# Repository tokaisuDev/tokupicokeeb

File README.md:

# Welcome to this keyboard's repo!

This is a Raspberry Pi Pico W-powered keyboard based on Stenokeyboard's Polyglot and 1upkeyboards' pi40.

Well, this is in the *beta* testing version so hopefully I can hear you guys' opinions on this, because this is my first time designing a PCB for a keyboard. Mistakes can be made...

Thanks for reading! And looking at this markdown file, I guess.

P/s: More info will be added later, I'm lazy

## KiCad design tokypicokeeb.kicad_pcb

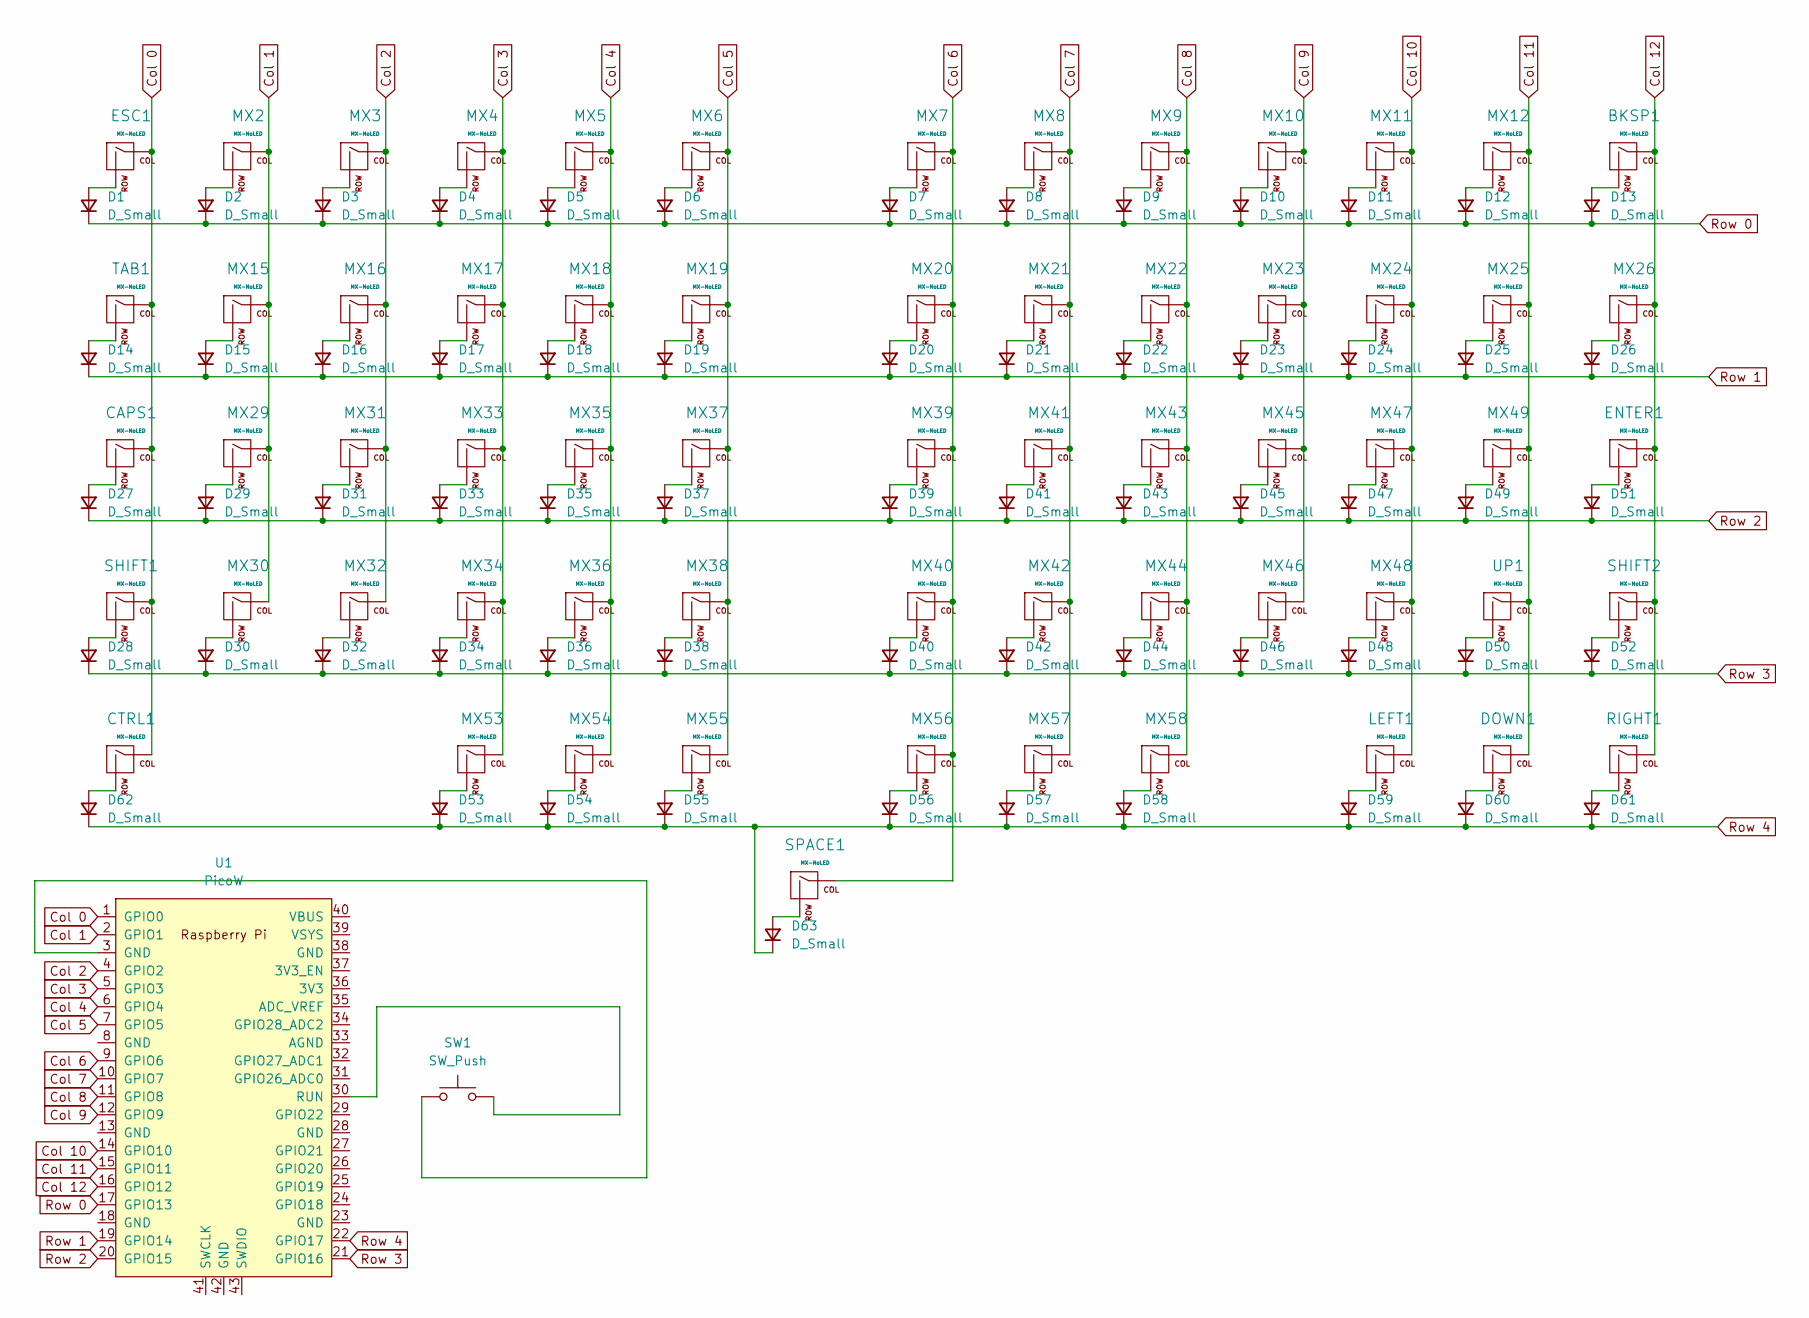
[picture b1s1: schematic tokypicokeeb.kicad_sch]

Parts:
BKSP1: MX-NoLED; MXOnly-2U-NoLED
CAPS1: MX-NoLED; MXOnly-1.75U-NoLED
CTRL1: MX-NoLED; MXOnly-1.25U-NoLED
D1, D2, D3, D4, D5, D6, D7, D8, D9, D10, D11, D12, D13, D14, D15, D16, D17, D18, D19, D20, D21, D22, D23, D24, D25, D26, D27, D28, D29, D30, D31, D32, D33, D34, D35, D36, D37, D38, D39, D40, D41, D42, D43, D44, D45, D46, D47, D48, D49, D50, D51, D52, D53, D54, D55, D56, D57, D58, D59, D60, D61, D62, D63: D_Small; Diode_DO-35
DOWN1: MX-NoLED; MXOnly-1U-NoLED
ENTER1: MX-NoLED; MXOnly-2.25U-NoLED
ESC1: MX-NoLED; MXOnly-1U-NoLED
LEFT1: MX-NoLED; MXOnly-1U-NoLED
MX2, MX3, MX4, MX5, MX6, MX7, MX8, MX9, MX10, MX11, MX12, MX15, MX16, MX17, MX18, MX19, MX20, MX21, MX22, MX23, MX24, MX25, MX29, MX30, MX31, MX32, MX33, MX34, MX35, MX36, MX37, MX38, MX39, MX40, MX41, MX42, MX43, MX44, MX45, MX46, MX47, MX48, MX49, MX53, MX54, MX55, MX56, MX57, MX58: MX-NoLED; MXOnly-1U-NoLED
MX26: MX-NoLED; MXOnly-1.5U-NoLED
RIGHT1: MX-NoLED; MXOnly-1U-NoLED
SHIFT1: MX-NoLED; MXOnly-2.25U-NoLED
SHIFT2: MX-NoLED; MXOnly-2.75U-NoLED
SPACE1: MX-NoLED; MXOnly-6.25U-NoLED
SW1: SW_Push; SKQG-1155865
TAB1: MX-NoLED; MXOnly-1.5U-NoLED
U1: PicoW; RPi_PicoW_SMD_TH
UP1: MX-NoLED; MXOnly-1U-NoLED

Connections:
Col 0: CAPS1.1 (COL), CTRL1.1 (COL), ESC1.1 (COL), SHIFT1.1 (COL), TAB1.1 (COL), U1.1 (GPIO0)
Col 1: MX2.1 (COL), MX15.1 (COL), MX29.1 (COL), MX30.1 (COL), U1.2 (GPIO1)
Col 2: MX3.1 (COL), MX16.1 (COL), MX31.1 (COL), MX32.1 (COL), U1.4 (GPIO2)
Col 3: MX4.1 (COL), MX17.1 (COL), MX33.1 (COL), MX34.1 (COL), MX53.1 (COL), U1.5 (GPIO3)
Col 4: MX5.1 (COL), MX18.1 (COL), MX35.1 (COL), MX36.1 (COL), MX54.1 (COL), U1.6 (GPIO4)
Col 5: MX6.1 (COL), MX19.1 (COL), MX37.1 (COL), MX38.1 (COL), MX55.1 (COL), U1.7 (GPIO5)
Col 6: MX7.1 (COL), MX20.1 (COL), MX39.1 (COL), MX40.1 (COL), MX56.1 (COL), SPACE1.1 (COL), U1.9 (GPIO6)
Col 7: MX8.1 (COL), MX21.1 (COL), MX41.1 (COL), MX42.1 (COL), MX57.1 (COL), U1.10 (GPIO7)
Col 8: MX9.1 (COL), MX22.1 (COL), MX43.1 (COL), MX44.1 (COL), MX58.1 (COL), U1.11 (GPIO8)
Col 9: MX10.1 (COL), MX23.1 (COL), MX45.1 (COL), MX46.1 (COL), U1.12 (GPIO9)
Col 10: LEFT1.1 (COL), MX11.1 (COL), MX24.1 (COL), MX47.1 (COL), MX48.1 (COL), U1.14 (GPIO10)
Col 11: DOWN1.1 (COL), MX12.1 (COL), MX25.1 (COL), MX49.1 (COL), U1.15 (GPIO11), UP1.1 (COL)
Col 12: BKSP1.1 (COL), ENTER1.1 (COL), MX26.1 (COL), RIGHT1.1 (COL), SHIFT2.1 (COL), U1.16 (GPIO12)
unnamed: BKSP1.2 (ROW), D13.2 (A)
unnamed: CAPS1.2 (ROW), D27.2 (A)
unnamed: CTRL1.2 (ROW), D62.2 (A)
unnamed: D1.2 (A), ESC1.2 (ROW)
unnamed: D2.2 (A), MX2.2 (ROW)
unnamed: D3.2 (A), MX3.2 (ROW)
unnamed: D4.2 (A), MX4.2 (ROW)
unnamed: D5.2 (A), MX5.2 (ROW)
unnamed: D6.2 (A), MX6.2 (ROW)
unnamed: D7.2 (A), MX7.2 (ROW)
unnamed: D8.2 (A), MX8.2 (ROW)
unnamed: D9.2 (A), MX9.2 (ROW)
unnamed: D10.2 (A), MX10.2 (ROW)
unnamed: D11.2 (A), MX11.2 (ROW)
unnamed: D12.2 (A), MX12.2 (ROW)
unnamed: D14.2 (A), TAB1.2 (ROW)
unnamed: D15.2 (A), MX15.2 (ROW)
unnamed: D16.2 (A), MX16.2 (ROW)
unnamed: D17.2 (A), MX17.2 (ROW)
unnamed: D18.2 (A), MX18.2 (ROW)
unnamed: D19.2 (A), MX19.2 (ROW)
unnamed: D20.2 (A), MX20.2 (ROW)
unnamed: D21.2 (A), MX21.2 (ROW)
unnamed: D22.2 (A), MX22.2 (ROW)
unnamed: D23.2 (A), MX23.2 (ROW)
unnamed: D24.2 (A), MX24.2 (ROW)
unnamed: D25.2 (A), MX25.2 (ROW)
unnamed: D26.2 (A), MX26.2 (ROW)
unnamed: D28.2 (A), SHIFT1.2 (ROW)
unnamed: D29.2 (A), MX29.2 (ROW)
unnamed: D30.2 (A), MX30.2 (ROW)
unnamed: D31.2 (A), MX31.2 (ROW)
unnamed: D32.2 (A), MX32.2 (ROW)
unnamed: D33.2 (A), MX33.2 (ROW)
unnamed: D34.2 (A), MX34.2 (ROW)
unnamed: D35.2 (A), MX35.2 (ROW)
unnamed: D36.2 (A), MX36.2 (ROW)
unnamed: D37.2 (A), MX37.2 (ROW)
unnamed: D38.2 (A), MX38.2 (ROW)
unnamed: D39.2 (A), MX39.2 (ROW)
unnamed: D40.2 (A), MX40.2 (ROW)
unnamed: D41.2 (A), MX41.2 (ROW)
unnamed: D42.2 (A), MX42.2 (ROW)
unnamed: D43.2 (A), MX43.2 (ROW)
unnamed: D44.2 (A), MX44.2 (ROW)
unnamed: D45.2 (A), MX45.2 (ROW)
unnamed: D46.2 (A), MX46.2 (ROW)
unnamed: D47.2 (A), MX47.2 (ROW)
unnamed: D48.2 (A), MX48.2 (ROW)
unnamed: D49.2 (A), MX49.2 (ROW)
unnamed: D50.2 (A), UP1.2 (ROW)
unnamed: D51.2 (A), ENTER1.2 (ROW)
unnamed: D52.2 (A), SHIFT2.2 (ROW)
unnamed: D53.2 (A), MX53.2 (ROW)
unnamed: D54.2 (A), MX54.2 (ROW)
unnamed: D55.2 (A), MX55.2 (ROW)
unnamed: D56.2 (A), MX56.2 (ROW)
unnamed: D57.2 (A), MX57.2 (ROW)
unnamed: D58.2 (A), MX58.2 (ROW)
unnamed: D59.2 (A), LEFT1.2 (ROW)
unnamed: D60.2 (A), DOWN1.2 (ROW)
unnamed: D61.2 (A), RIGHT1.2 (ROW)
unnamed: D63.2 (A), SPACE1.2 (ROW)
unnamed: SW1.1, U1.3 (GND)
unnamed: SW1.2, U1.30 (RUN)
Row 0: D1.1 (K), D2.1 (K), D3.1 (K), D4.1 (K), D5.1 (K), D6.1 (K), D7.1 (K), D8.1 (K), D9.1 (K), D10.1 (K), D11.1 (K), D12.1 (K), D13.1 (K), U1.17 (GPIO13)
Row 1: D14.1 (K), D15.1 (K), D16.1 (K), D17.1 (K), D18.1 (K), D19.1 (K), D20.1 (K), D21.1 (K), D22.1 (K), D23.1 (K), D24.1 (K), D25.1 (K), D26.1 (K), U1.19 (GPIO14)
Row 2: D27.1 (K), D29.1 (K), D31.1 (K), D33.1 (K), D35.1 (K), D37.1 (K), D39.1 (K), D41.1 (K), D43.1 (K), D45.1 (K), D47.1 (K), D49.1 (K), D51.1 (K), U1.20 (GPIO15)
Row 3: D28.1 (K), D30.1 (K), D32.1 (K), D34.1 (K), D36.1 (K), D38.1 (K), D40.1 (K), D42.1 (K), D44.1 (K), D46.1 (K), D48.1 (K), D50.1 (K), D52.1 (K), U1.21 (GPIO16)
Row 4: D53.1 (K), D54.1 (K), D55.1 (K), D56.1 (K), D57.1 (K), D58.1 (K), D59.1 (K), D60.1 (K), D61.1 (K), D62.1 (K), D63.1 (K), U1.22 (GPIO17)

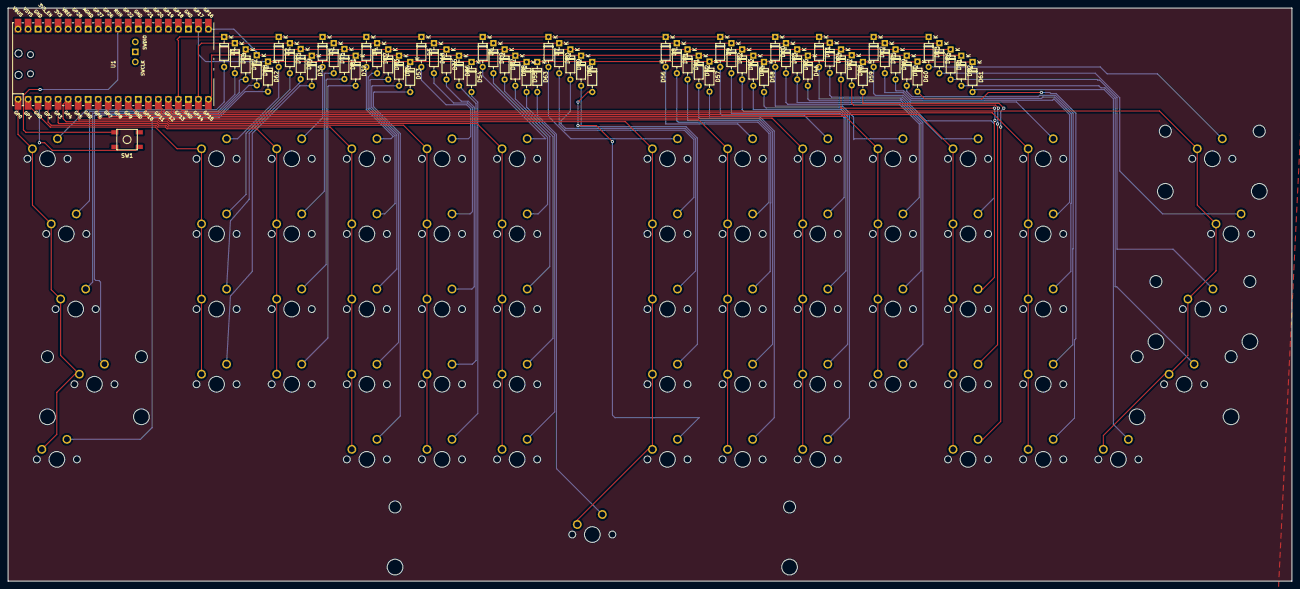
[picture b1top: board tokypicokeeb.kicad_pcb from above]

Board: 2 copper layers, 325.4 x 145.3 mm, 128 parts (0 on the bottom side), 83 nets.

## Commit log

2023-10-21 inintialize
2023-10-21 next
2023-10-22 Add submodules
2023-10-22 next 2
2023-10-22 adding some stuff
2023-10-24 add some symbols?
2023-10-26 updated matrix
2023-10-27 re-organized things
2023-10-29 pcb stage 1
2023-10-30 duplex trigger
2023-10-31 nah 2
2023-11-02 ehhhhh
2023-11-02 scottokeebs oriented
2023-11-05 1/2 diodes
2023-11-09 finished the diodes placement
2023-11-13 finished ver. 1
